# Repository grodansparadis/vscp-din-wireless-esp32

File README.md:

# vscp-din-wireless-esp32
ESP32 based wifi/bt VSCP controller in a single module DIN package

**Note!** This is still a prototype.

## PCB's

---

Part of the [VSCP Project](https://www.vscp.org).

Copyright 2021-2022 © Åke Hedman, (Grodans Paradis AB)[https://www.grodansparadis.com]

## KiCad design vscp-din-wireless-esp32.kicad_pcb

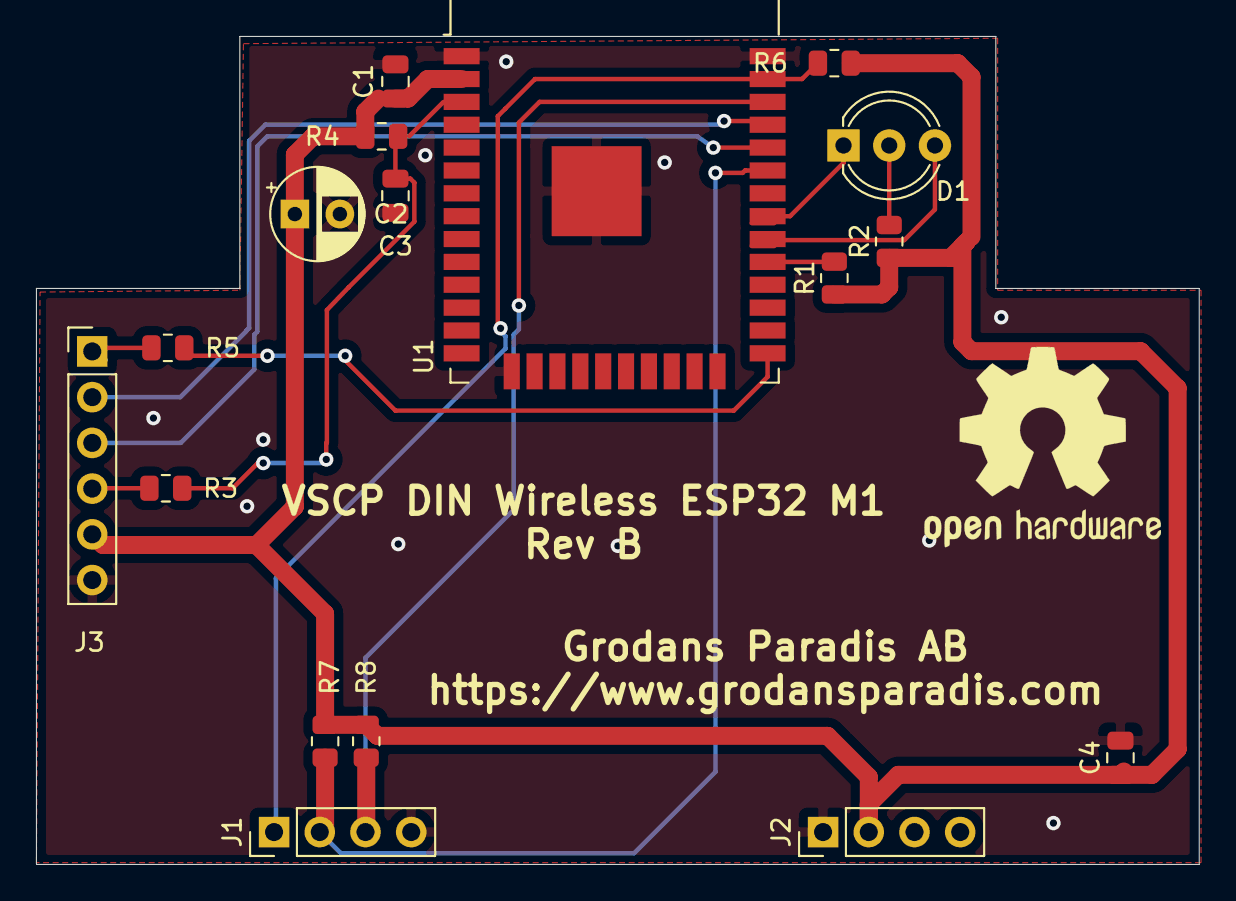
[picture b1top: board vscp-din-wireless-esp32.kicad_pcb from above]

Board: 2 copper layers, 64.6 x 46.0 mm, 17 parts (0 on the bottom side), 15 nets.

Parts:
C1, C3, C4: 100nF; C_0805_2012Metric
C2: 10uF; CP_Radial_D5.0mm_P2.50mm
D1: LED_Dual_CAC; LED_D5.0mm-3
J1: Conn_Left_I2C; PinHeader_1x04_P2.54mm_Vertical
J2: Conn_Right_Power; PinHeader_1x04_P2.54mm_Vertical
J3: Conn_01x06; PinHeader_1x06_P2.54mm_Vertical
R1, R4, R6: 10K; R_0805_2012Metric
R2, R3, R5: 470; R_0805_2012Metric
R7, R8: 4k7; R_0805_2012Metric
U1: ESP32-WROOM-32D; ESP32-WROOM-32

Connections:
/FLASH: J3.1, R5.2
/RESET: J3.4, R3.1
/RXD: J3.3, U1.34
/TXD: J3.2, U1.35
/irq: J1.1, R6.1, U1.37
/leda: D1.3, U1.30
/ledb: D1.1, U1.31
/reset: C3.1, R3.2, R4.2, U1.3
/scl: J1.3, R8.1, U1.36
/sda: J1.2, R7.1, U1.33
GND: C1.2, C2.2, C3.2, C4.2, J1.4, J2.1, J3.6, U1.1, U1.15, U1.38, U1.39
unnamed: D1.2, R2.2
unnamed: R1.2, U1.29
unnamed: R5.1, U1.25
VCC: C1.1, C2.1, C4.1, J2.2, J3.5, R1.1, R2.1, R4.1, R6.2, R7.2, R8.2, U1.2

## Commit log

2021-05-24 Initial import
2021-05-24 Fixed module name
2021-05-24 Changed front silicon
2021-05-25 Fixed board to board connector
2021-05-25 Adding gerbers
2021-05-25 Added some info
2021-08-09 srinked board to fit enclosure
2022-02-03 Updated copyright
